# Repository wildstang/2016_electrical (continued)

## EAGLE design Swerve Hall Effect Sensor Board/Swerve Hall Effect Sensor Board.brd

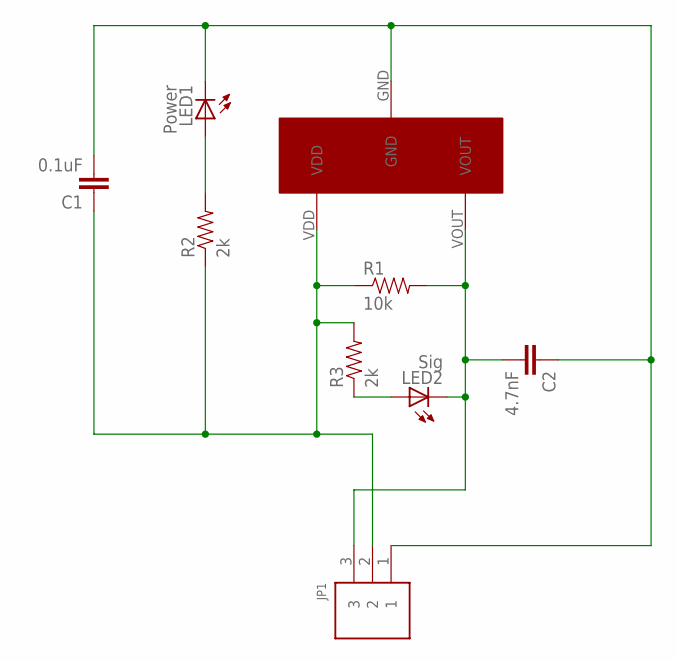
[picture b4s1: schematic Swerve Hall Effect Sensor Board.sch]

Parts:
C1: 0.1uF; 0603-CAP
C2: 4.7nF; 0603-CAP
JP1: 3PIN; B3B-PH-K-S
LED1: Power; LED-0603
LED2: Sig; LED-0603
R1: 10k; 0603-RES
R2, R3: 2k; 0603-RES
U$1: US5881-HALL-EFFECT

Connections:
GND: C1.2, C2.1, JP1.1, LED1.C, U$1.GND
unnamed: LED1.A, R2.2
unnamed: LED2.A, R3.1
SIGNAL: C2.2, JP1.3, LED2.C, R1.2, U$1.VOUT
VDD: C1.1, JP1.2, R1.1, R2.1, R3.2, U$1.VDD

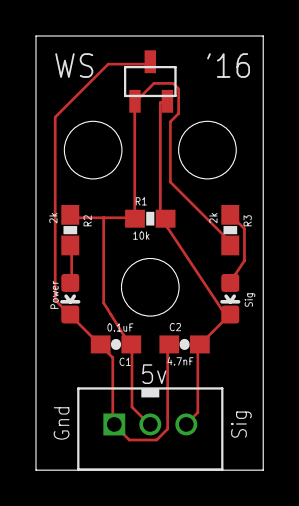
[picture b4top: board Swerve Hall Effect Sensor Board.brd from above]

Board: 2 copper layers, 12.6 x 24.1 mm, 9 parts (0 on the bottom side), 5 nets.

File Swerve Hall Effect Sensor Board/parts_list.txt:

Partlist

Exported from Hall Effect Sensor.sch at 2/4/2015 12:23:07 PM

EAGLE Version 7.1.0 Copyright (c) 1988-2014 CadSoft

Assembly variant: 

Part     Value              Device             Package            Library             Sheet

C1       0.1uF              CAP0603-CAP        0603-CAP           SparkFun-Passives   1
C2       4.7nF              CAP0603-CAP        0603-CAP           SparkFun-Passives   1
JP1                         M03PTH             1X03               SparkFun-Connectors 1
LED1     Power              LED0603            LED-0603           SparkFun-LED        1
LED2     Sig                LED0603            LED-0603           SparkFun-LED        1
R1       10k                RESISTOR0603-RES   0603-RES           SparkFun-Passives   1
R2       2k                 RESISTOR0603-RES   0603-RES           SparkFun-Passives   1
R3       2k                 RESISTOR0603-RES   0603-RES           SparkFun-Passives   1
U$1      US5881-HALL-EFFECT US5881-HALL-EFFECT US5881-HALL-EFFECT TPS5430             1

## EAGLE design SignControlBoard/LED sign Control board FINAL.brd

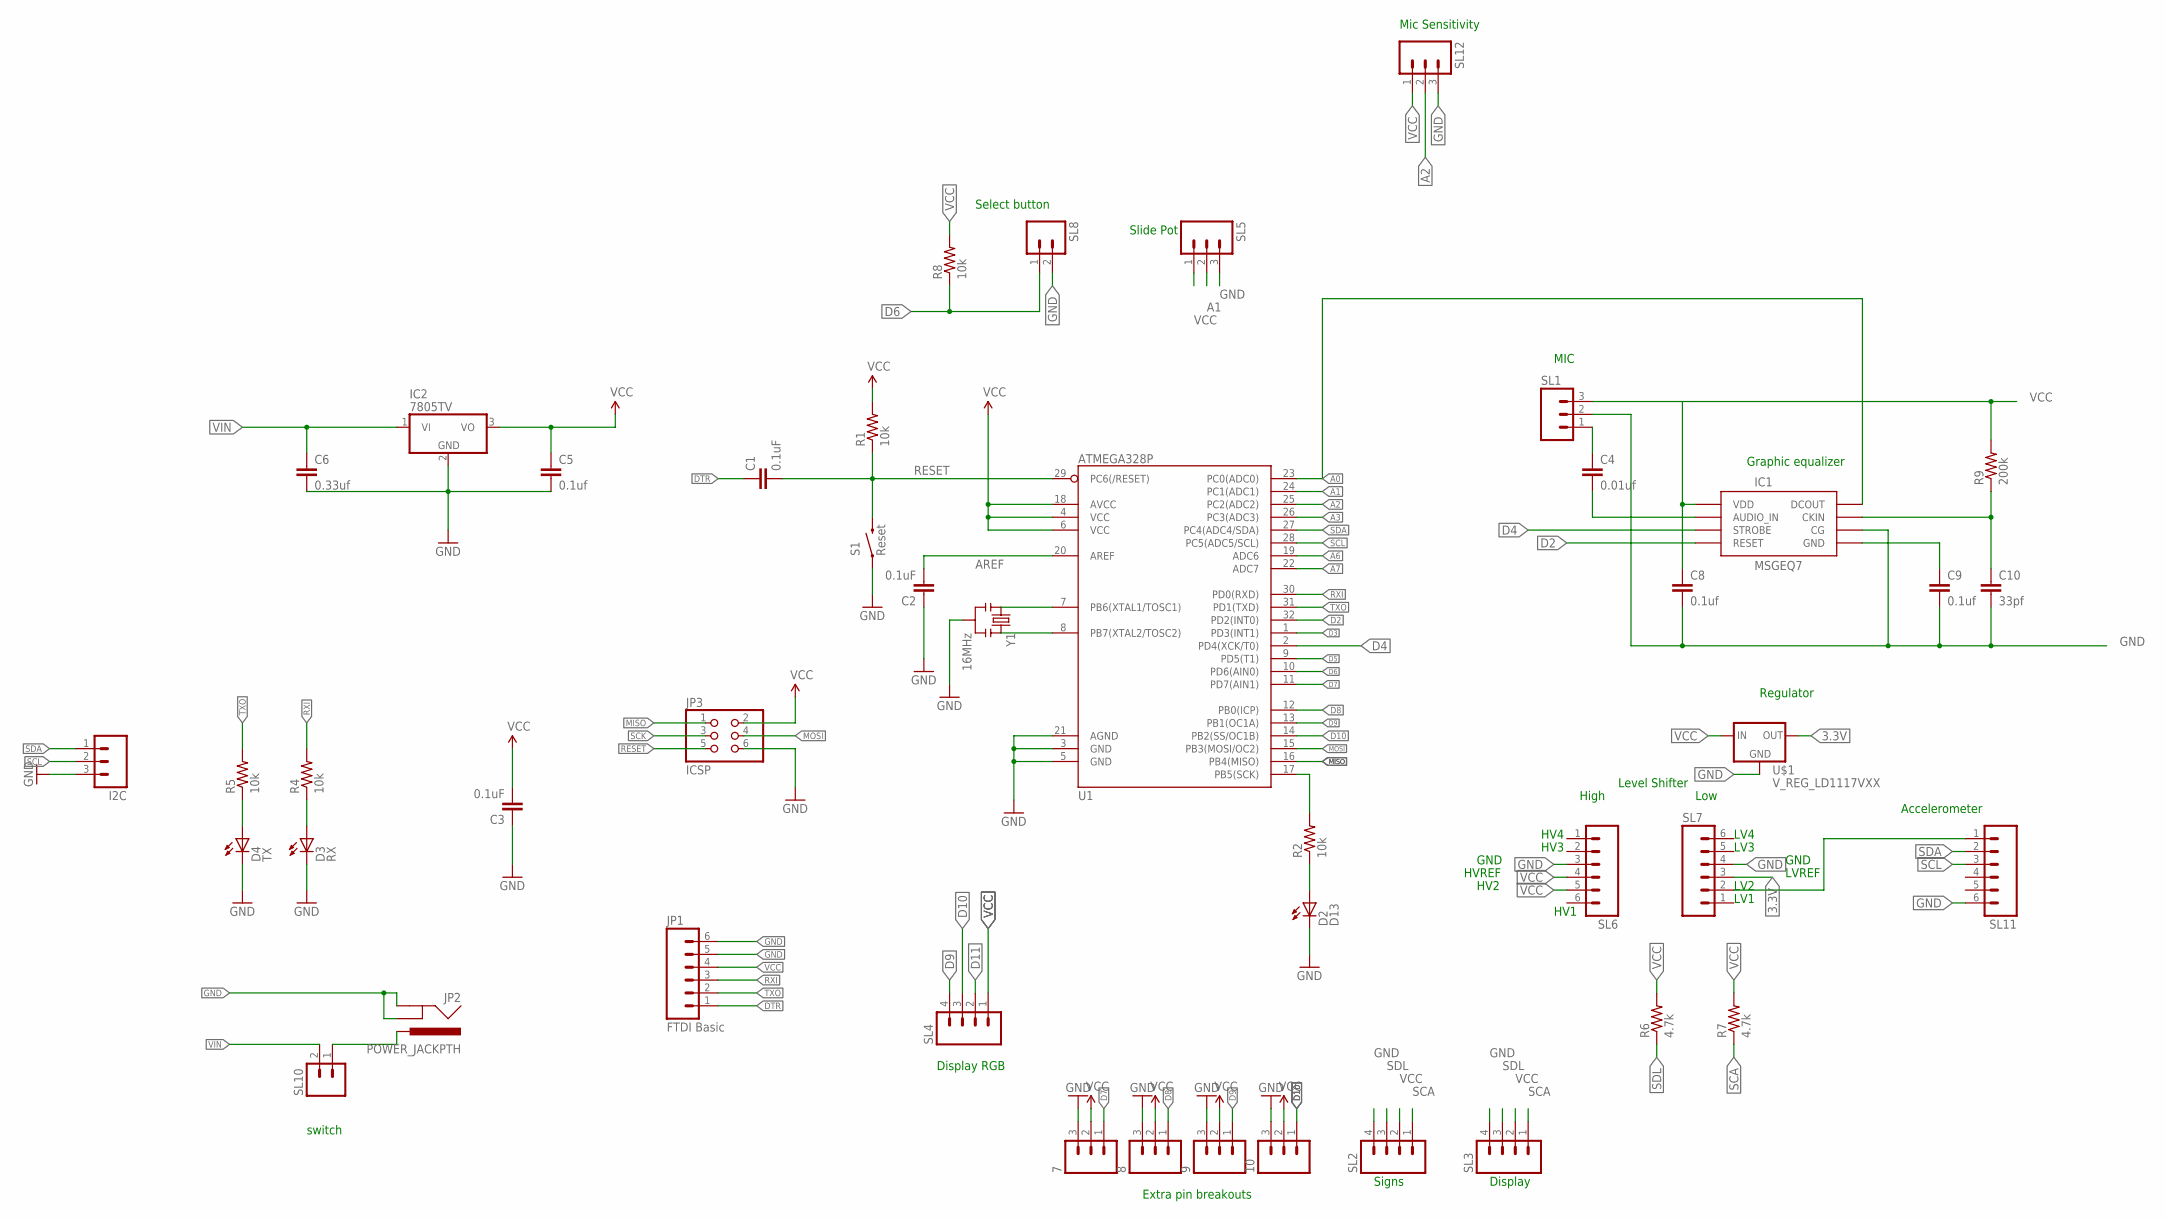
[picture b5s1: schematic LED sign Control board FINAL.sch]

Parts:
7, 8, 9, 10: M03PTH; 1X03
C1, C2, C3: 0.1uF; 0603-CAP
C4: 0.01uf; C2.5-3
C5, C8, C9: 0.1uf; C2.5-3
C6: 0.33uf; C2.5-3
C10: 33pf; C2.5-3
D2: D13; LED-0603
D3: RX; LED-0603
D4: TX; LED-0603
I2C: M03PTH; 1X03
IC1: MSGEQ7DIL; DIL-08
IC2: 7805TV; TO220V
JP1: FTDI Basic; 1X06
JP2: POWER_JACKPTH; POWER_JACK_PTH
JP3: ICSP; 2X03
R1, R2, R4, R5: 10k; 0603-RES
R6, R7: 4.7k; 1206
R8: 10k; 1206
R9: 200k; 1206
S1: Reset; TACTILE_SWITCH_SMD
SL1, SL5, SL12: M03; 03P
SL2, SL3, SL4: M04; 04P
SL6, SL7, SL11: M06; 06P
SL8, SL10: M02; 02P
U1: ATMEGA328P; TQFP32-08
U$1: V_REG_LD1117VXX; 78XXL
Y1: 16MHz; RESONATOR-SMD

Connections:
3.3V: SL7.3, U$1.GND (OUT)
A0: IC1.3 (DCOUT), U1.23 (PC0(ADC0))
A1: SL5.2, U1.24 (PC1(ADC1))
A2: SL12.2, U1.25 (PC2(ADC2))
A3: U1.26 (PC3(ADC3))
A6: U1.19 (ADC6)
A7: U1.22 (ADC7)
AREF: C2.2, U1.20 (AREF)
D2: IC1.7 (RESET), U1.32 (PD2(INT0))
D3: U1.1 (PD3(INT1))
D4: IC1.4 (STROBE), U1.2 (PD4(XCK/T0))
D5: U1.9 (PD5(T1))
D6: R8.1, SL8.1, U1.10 (PD6(AIN0))
D7: 7.1, U1.11 (PD7(AIN1))
D8: 8.1, U1.12 (PB0(ICP))
D9: 9.1, SL4.4, U1.13 (PB1(OC1A))
D10: 10.1, SL4.3, U1.14 (PB2(SS/OC1B))
D11: SL4.2
DTR: C1.1, JP1.1
GND: 7.3, 8.3, 9.3, 10.3, C2.1, C3.1, C5.2, C6.2, C8.2, C9.2, C10.2, D2.C, D3.C, D4.C, I2C.3, IC1.6 (CG), IC2.2 (GND), JP1.5, JP1.6, JP2.GND, JP2.GNDBREAK, JP3.6, S1.1, SL1.2, SL2.4, SL3.4, SL5.3, SL6.3, SL7.4, SL8.2, SL11.6, SL12.3, U1.3 (GND), U1.5 (GND), U1.21 (AGND), U$1.IN (GND), Y1.2
MISO: JP3.1, U1.16 (PB4(MISO))
MOSI: JP3.4, U1.15 (PB3(MOSI/OC2))
unnamed: U1.7 (PB6(XTAL1/TOSC1)), Y1.1
unnamed: U1.8 (PB7(XTAL2/TOSC2)), Y1.3
unnamed: D2.A, R2.1
unnamed: D3.A, R4.1
unnamed: D4.A, R5.1
unnamed: JP2.PWR, SL10.1
unnamed: C4.1, SL1.1
unnamed: C4.2, IC1.5 (AUDIO_IN)
unnamed: C9.1, IC1.2 (GND)
unnamed: C10.1, IC1.8 (CKIN), R9.1
unnamed: R2.2, U1.17 (PB5(SCK))
unnamed: SL7.2, SL11.1
RESET: C1.2, JP3.5, R1.1, S1.3 (2), U1.29 (PC6(/RESET))
RXI: JP1.3, R4.2, U1.30 (PD0(RXD))
SCA: R7.1, SL2.1, SL3.1
SCK: JP3.3
SCL: I2C.2, SL11.3, U1.28 (PC5(ADC5/SCL))
SDA: I2C.1, SL11.2, U1.27 (PC4(ADC4/SDA))
SDL: R6.1, SL2.3, SL3.3
TXO: JP1.2, R5.2, U1.31 (PD1(TXD))
VCC: 7.2, 8.2, 9.2, 10.2, C3.2, C5.1, C8.1, IC1.1 (VDD), IC2.3 (VO), JP1.4, JP3.2, R1.2, R6.2, R7.2, R8.2, R9.2, SL1.3, SL2.2, SL3.2, SL4.1, SL5.1, SL6.4, SL6.5, SL12.1, U1.4 (VCC), U1.6 (VCC), U1.18 (AVCC), U$1.OUT (IN)
VIN: C6.1, IC2.1 (VI), SL10.2

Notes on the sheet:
Accelerometer
Slide Pot
Display
Signs
Level Shifter
High
Low
Select button
Regulator
MIC
Graphic equalizer
Extra pin breakouts
HV1
HV2
HV3
HV4
HVREF
GND
LV1
LV2
LVREF
LV3
LV4
Display RGB
Mic Sensitivity
switch

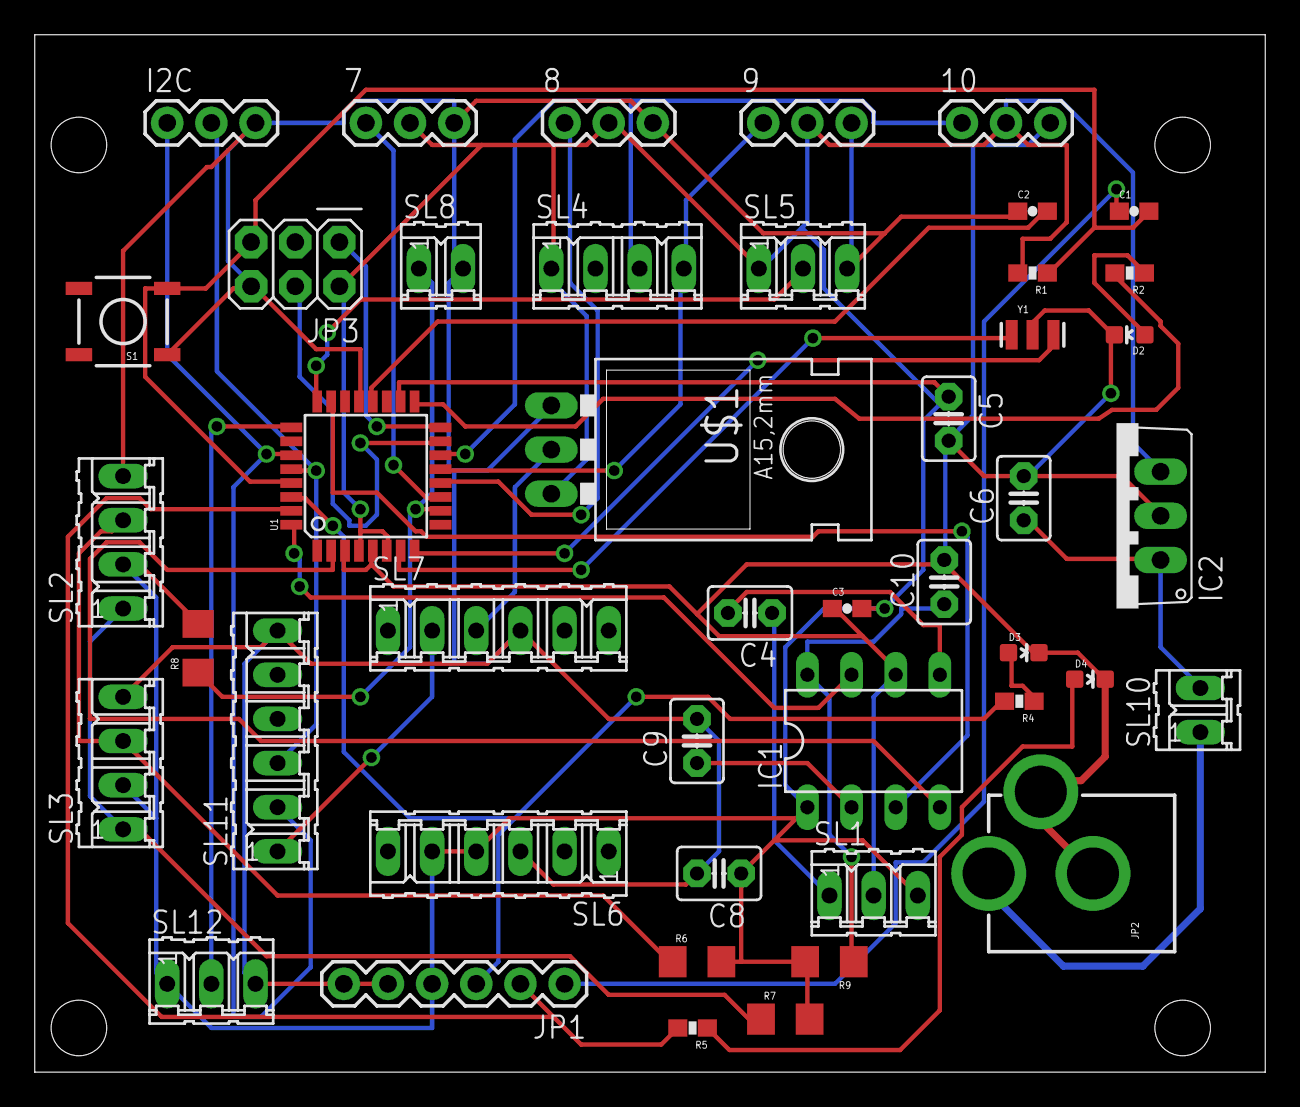
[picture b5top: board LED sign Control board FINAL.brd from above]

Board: 2 copper layers, 70.8 x 59.7 mm, 45 parts (0 on the bottom side), 37 nets.

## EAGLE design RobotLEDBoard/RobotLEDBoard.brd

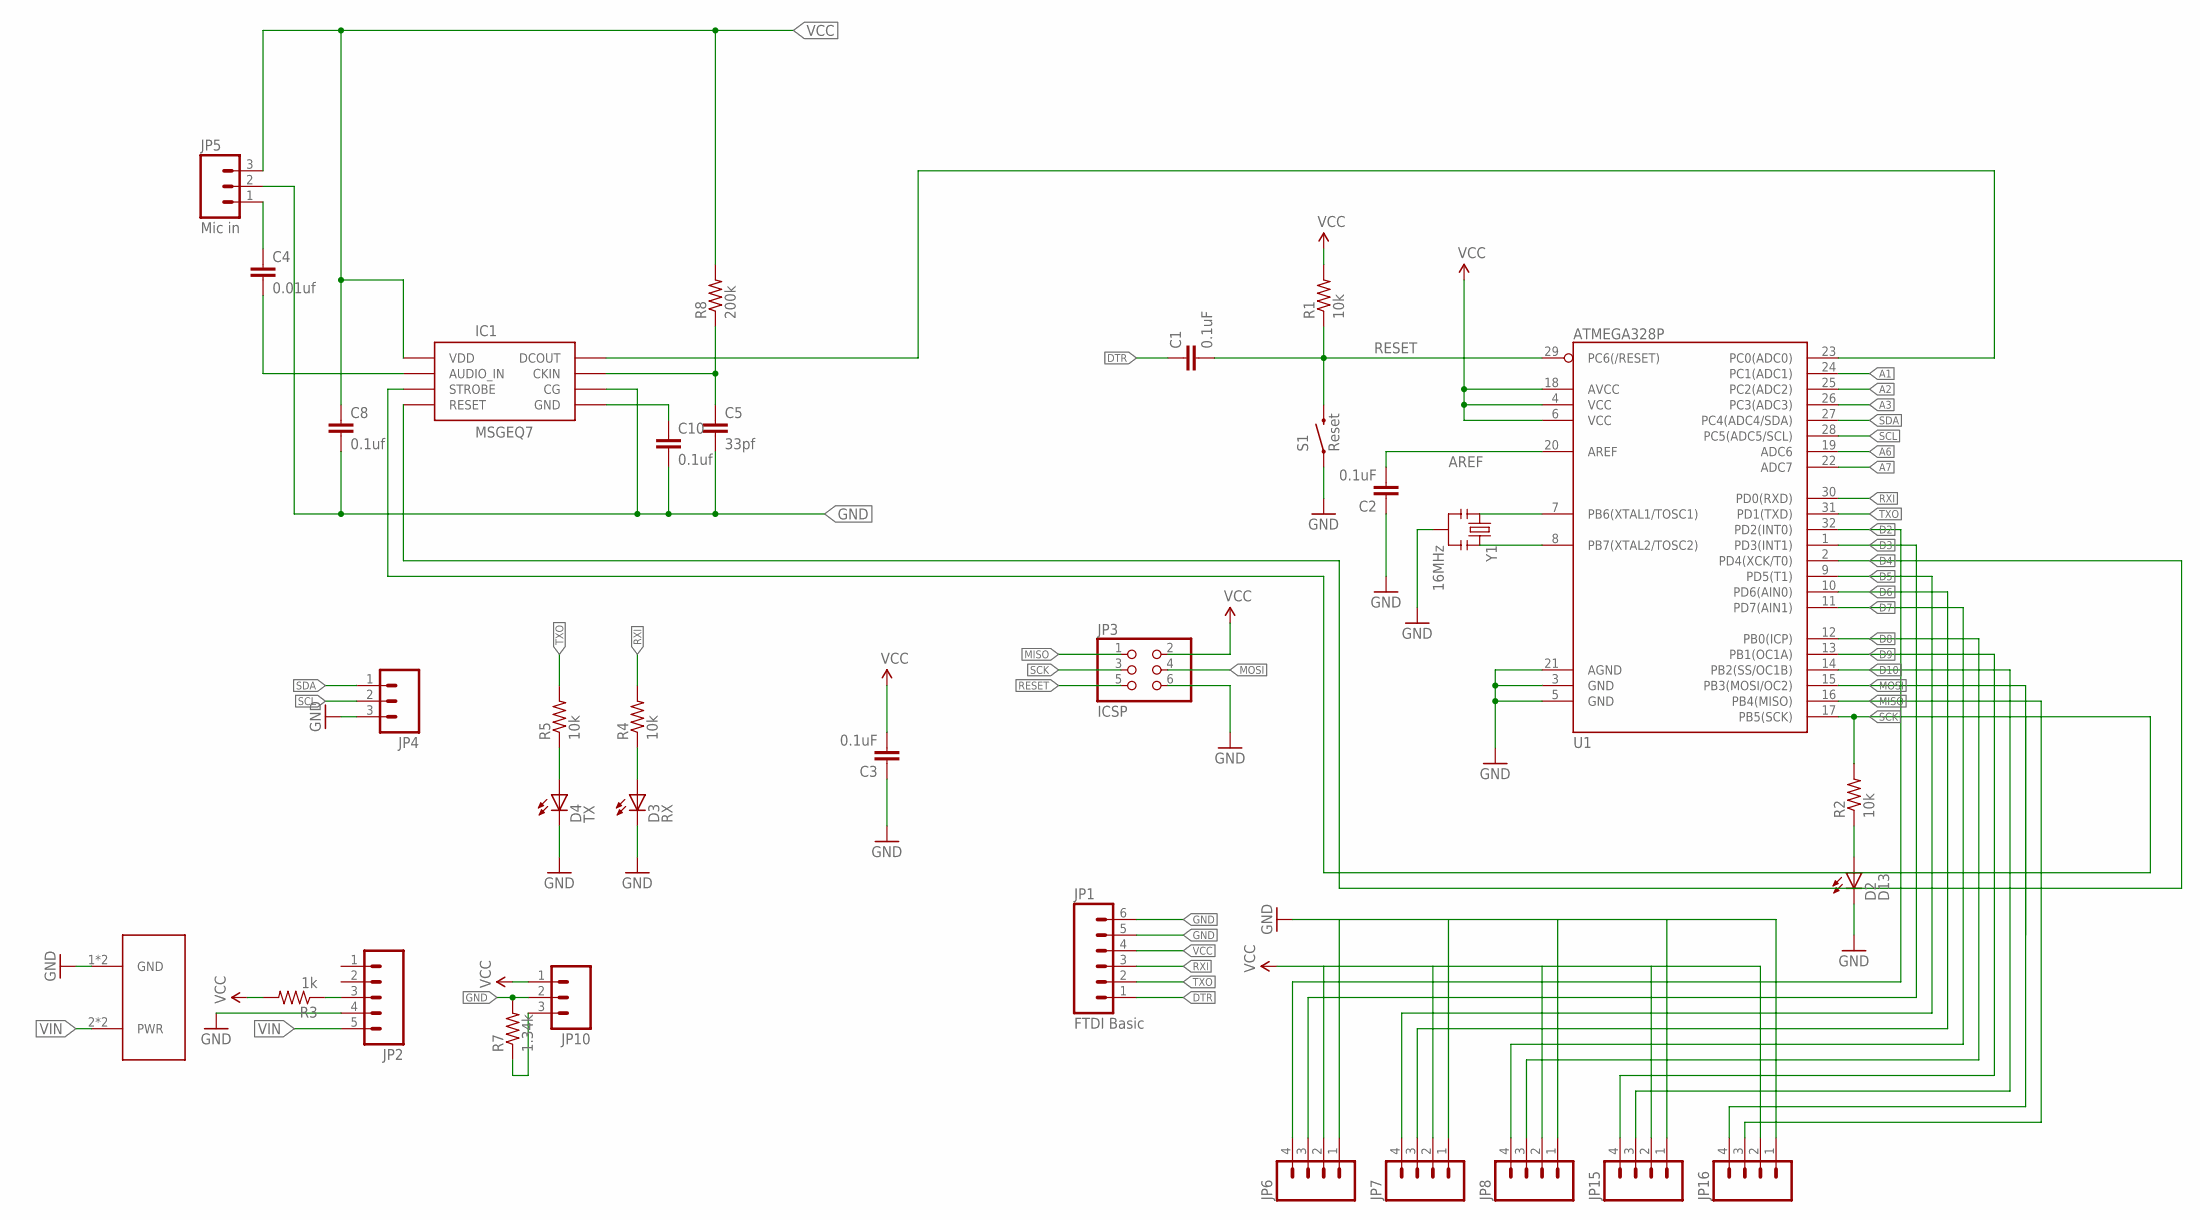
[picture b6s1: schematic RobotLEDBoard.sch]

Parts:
C1, C2, C3: 0.1uF; 0603-CAP
C4: 0.01uf; C0402
C5: 33pf; C0201
C8, C10: 0.1uf; C0603
D2: D13; LED-0603
D3: RX; LED-0603
D4: TX; LED-0603
IC1: MSGEQ7; DIP08
JP1: FTDI Basic; 1X06
JP2: M05PTH; 1X05
JP3: ICSP; 2X03
JP4, JP10: M03PTH; 1X03
JP5: Mic in; 1X03
JP6, JP7, JP8, JP15, JP16: M04PTH; 1X04
R1, R2, R4, R5: 10k; 0603-RES
R3: 1k; AXIAL-0.3
R7: 1.34k; AXIAL-0.3
R8: 200k; M1206
S1: Reset; TACTILE_SWITCH_SMD
U1: ATMEGA328P; TQFP32-08
U$1: LSF-SMT
Y1: 16MHz; RESONATOR-SMD

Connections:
A0: IC1.3 (DCOUT), U1.23 (PC0(ADC0))
A1: U1.24 (PC1(ADC1))
A2: U1.25 (PC2(ADC2))
A3: U1.26 (PC3(ADC3))
A6: U1.19 (ADC6)
A7: U1.22 (ADC7)
AREF: C2.2, U1.20 (AREF)
D2: JP6.4, U1.32 (PD2(INT0))
D3: JP6.3, U1.1 (PD3(INT1))
D4: IC1.7 (RESET), U1.2 (PD4(XCK/T0))
D5: JP7.4, U1.9 (PD5(T1))
D6: JP7.3, U1.10 (PD6(AIN0))
D7: JP8.4, U1.11 (PD7(AIN1))
D8: JP8.3, U1.12 (PB0(ICP))
D9: JP15.4
D10: JP15.3, U1.14 (PB2(SS/OC1B))
DTR: C1.1, JP1.1
GND: C2.1, C3.1, C5.2, C8.2, C10.2, D2.C, D3.C, D4.C, IC1.2 (CG), JP1.5, JP1.6, JP2.4, JP3.6, JP4.3, JP5.2, JP6.1, JP7.1, JP8.1, JP10.2, JP15.1, JP16.1, R7.P$2 (2), S1.1, U1.3 (GND), U1.5 (GND), U1.21 (AGND), U$1.1 (GND), U$1.1-2 (GND), Y1.2
MISO: JP3.1, JP16.3, U1.16 (PB4(MISO))
MOSI: JP3.4, JP16.4, U1.15 (PB3(MOSI/OC2))
unnamed: U1.7 (PB6(XTAL1/TOSC1)), Y1.1
unnamed: U1.8 (PB7(XTAL2/TOSC2)), Y1.3
unnamed: JP2.3, R3.P$1 (1)
unnamed: D2.A, R2.1
unnamed: D3.A, R4.1
unnamed: D4.A, R5.1
unnamed: JP10.3, R7.P$1 (1)
unnamed: C5.1, IC1.8 (CKIN), R8.1
unnamed: C4.1, JP5.1
unnamed: C4.2, IC1.5 (AUDIO_IN)
unnamed: C10.1, IC1.6 (GND)
RESET: C1.2, JP3.5, R1.1, S1.3 (2), U1.29 (PC6(/RESET))
RXI: JP1.3, R4.2, U1.30 (PD0(RXD))
SCK: IC1.4 (STROBE), JP3.3, R2.2, U1.17 (PB5(SCK))
SCL: JP4.2, U1.28 (PC5(ADC5/SCL))
SDA: JP4.1, U1.27 (PC4(ADC4/SDA))
TXO: JP1.2, R5.2, U1.31 (PD1(TXD))
VCC: C3.2, C8.1, IC1.1 (VDD), JP1.4, JP3.2, JP5.3, JP6.2, JP7.2, JP8.2, JP10.1, JP15.2, JP16.2, R1.2, R3.P$2 (2), R8.2, U1.4 (VCC), U1.6 (VCC), U1.18 (AVCC)
VIN: JP2.5, U$1.2 (PWR), U$1.2-2 (PWR)

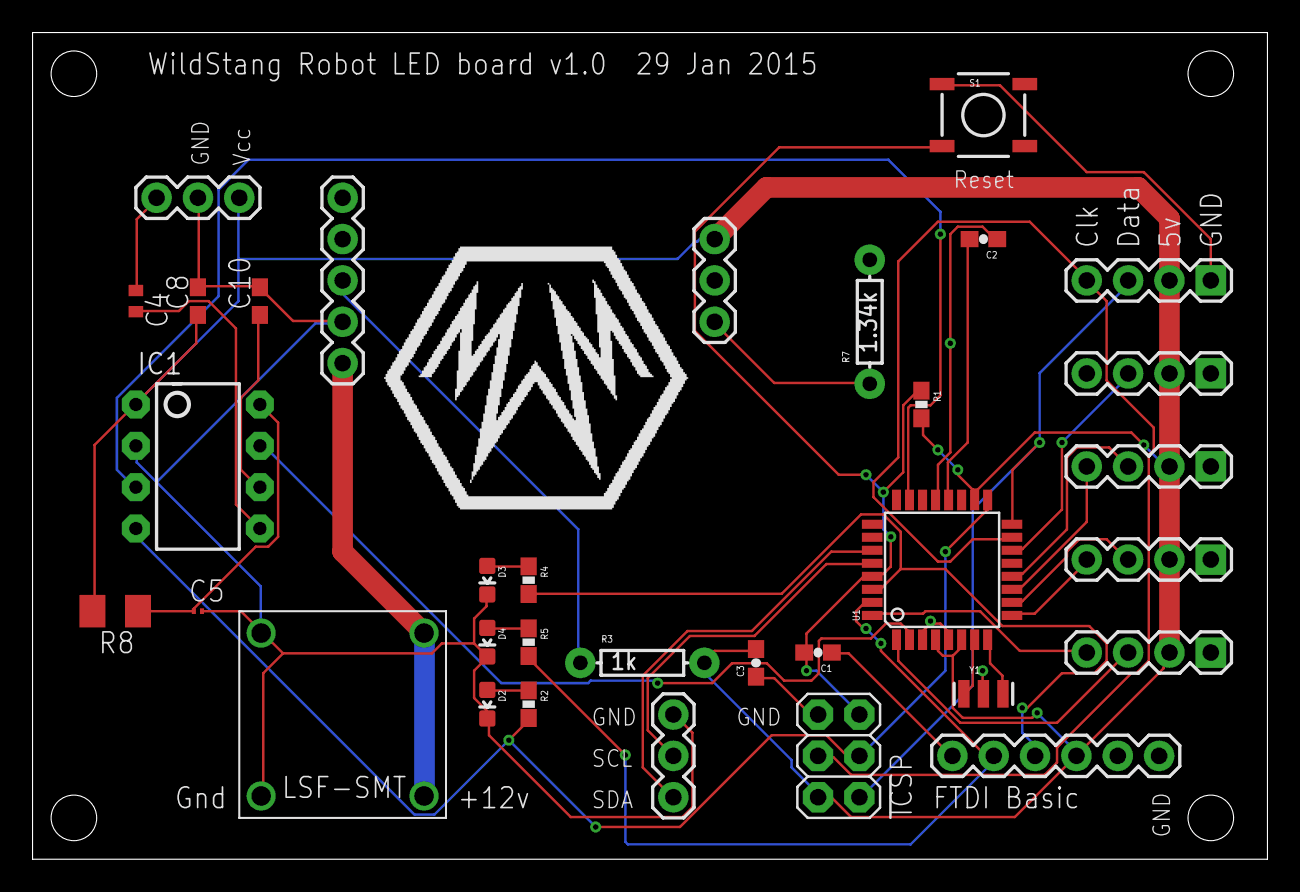
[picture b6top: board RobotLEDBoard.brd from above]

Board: 2 copper layers, 75.9 x 50.8 mm, 33 parts (0 on the bottom side), 33 nets.

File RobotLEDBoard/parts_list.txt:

Partlist

Exported from RobotLEDBoard.sch at 2/4/2015 12:23:42 PM

EAGLE Version 7.1.0 Copyright (c) 1988-2014 CadSoft

Assembly variant: 

Part     Value          Device                Package            Library                    Sheet

C1       0.1uF          CAP0603-CAP           0603-CAP           SparkFun-Passives          1
C2       0.1uF          CAP0603-CAP           0603-CAP           SparkFun-Passives          1
C3       0.1uF          CAP0603-CAP           0603-CAP           SparkFun-Passives          1
C4       0.01uf         CC0402                C0402              eagle-ltspice              1
C5       33pf           CC0201                C0201              eagle-ltspice              1
C8       0.1uf          CC0603                C0603              eagle-ltspice              1
C10      0.1uf          CC0603                C0603              eagle-ltspice              1
D2       D13            LED-RED0603           LED-0603           SparkFun-LED               1
D3       RX             LED-GREEN0603         LED-0603           SparkFun-LED               1
D4       TX             LED-RED0603           LED-0603           SparkFun-LED               1
IC1      MSGEQ7         MSGEQ7                DIP08              SparkFun-AnalogIC          1
JP1      FTDI Basic     M06SIP                1X06               SparkFun-Connectors        1
JP2                     M05PTH                1X05               SparkFun-Connectors        1
JP3      ICSP           PINHD-2X3             2X03               SparkFun-Connectors        1
JP4                     M03PTH                1X03               SparkFun-Connectors        1
JP5      Mic in         M03PTH                1X03               SparkFun-Connectors        1
JP6                     M04PTH                1X04               SparkFun-Connectors        1
JP7                     M04PTH                1X04               SparkFun-Connectors        1
JP8                     M04PTH                1X04               SparkFun-Connectors        1
JP10                    M03PTH                1X03               SparkFun-Connectors        1
JP15                    M04PTH                1X04               SparkFun-Connectors        1
JP16                    M04PTH                1X04               SparkFun-Connectors        1
R1       10k            RESISTOR0603-RES      0603-RES           SparkFun-Passives          1
R2       10k            RESISTOR0603-RES      0603-RES           SparkFun-Passives          1
R3       1k             RESISTORAXIAL-0.3     AXIAL-0.3          SparkFun-Resistors         1
R4       10k            RESISTOR0603-RES      0603-RES           SparkFun-Passives          1
R5       10k            RESISTOR0603-RES      0603-RES           SparkFun-Passives          1
R7       1.34k          RESISTORAXIAL-0.3     AXIAL-0.3          SparkFun-Resistors         1
R8       200k           R-US_M1206            M1206              rcl                        1
S1       Reset          SWITCH-MOMENTARY-2SMD TACTILE_SWITCH_SMD SparkFun-Electromechanical 1
U$1      LSF-SMT        LSF-SMT               LSF-SMT            LSF-SMT                    1
U1       ATMEGA328P     ATMEGA328_SMT         TQFP32-08          SparkFun-DigitalIC         1
Y1       16MHz          RESONATOR16MHZ        RESONATOR-SMD      SparkFun-FreqCtrl          1

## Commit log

2015-09-27 Added 2015 files to seed 2016
2015-12-09 Updated LED Boards
2015-12-09 Updated LED sign boards
2016-01-27 Added finalized sign control boards
2016-01-28 Added LED Sign boards
2016-01-28 Made traces on power thicker
2016-01-28 Finalized board
2016-01-30 Updated control and sign boards. Removed old versions
2016-02-02 Added comment for git practice
2016-02-08 Added LED code for driver tryouts
2016-02-10 Updated sign boards
2016-03-14 added arduino code.
2016-03-21 New boards and updated code
2016-03-29 Sides now always display a color that corresponds with turbo/antiturbo
2016-04-08 Added functions for on target, flywheel on, and flywheel full speed.
